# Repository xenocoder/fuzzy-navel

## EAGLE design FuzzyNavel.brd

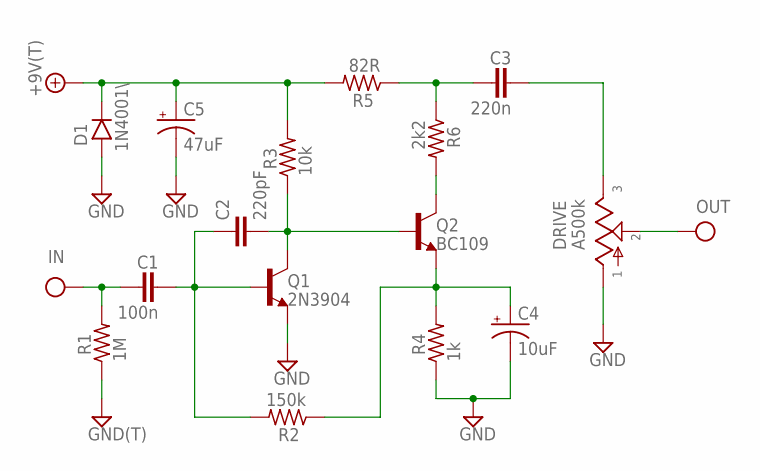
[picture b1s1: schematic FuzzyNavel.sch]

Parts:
+9V: +9V(T); SQUARE
C1: 100n; 072X025
C2: 220pF; 050X030_050_1
C3: 220n; 072X035
C4: 10uF; 050_020_1
C5: 47uF; 050_020_1
D1: 1N4001\; DO41-2
DRIVE: A500k; 16MM_PCB_PADS
GND: GND(T); SQUARE
IN: IN(T); SQUARE
OUT: OUT(T); SQUARE
Q1: 2N3904; TO92-
Q2: BC109; TO92-
R1: 1M; R0207/3
R2: 150k; R0207/3
R3: 10k; R0207/3
R4: 1k; R0207/3
R5: 82R; R0207/3
R6: 2k2; R0207/3

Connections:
+9V: +9V.1, C5.+, D1.C, R3.2, R5.2
GND: C4.-, C5.-, D1.A, DRIVE.1, GND.1, Q1.3 (E), R1.1, R4.1
IN: C1.1, IN.1, R1.2
unnamed: C2.2, Q1.1 (C), Q2.2 (B), R3.1
unnamed: C1.2, C2.1, Q1.2 (B), R2.2
unnamed: C4.+, Q2.3 (E), R2.1, R4.2
unnamed: Q2.1 (C), R6.2
unnamed: C3.1, R5.1, R6.1
unnamed: C3.2, DRIVE.3
OUT: DRIVE.2, OUT.1

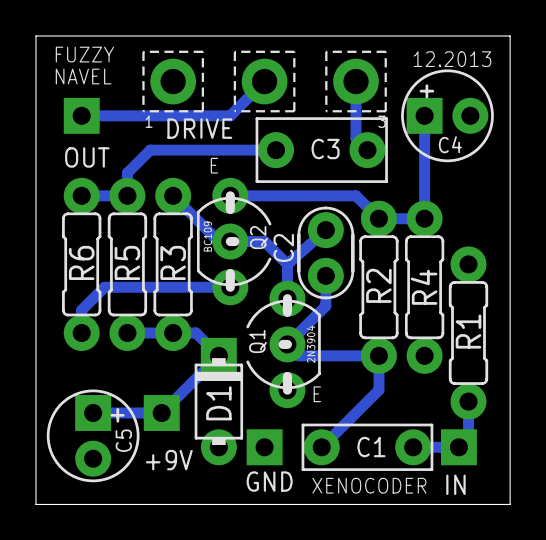
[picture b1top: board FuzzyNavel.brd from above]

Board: 2 copper layers, 26.3 x 26.0 mm, 19 parts (0 on the bottom side), 10 nets.

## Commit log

2015-10-08 Initial upload
